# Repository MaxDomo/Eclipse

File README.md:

# Projet Eclipse

Bienvenue sur ce projet de motorisation de la lampe IKEA modèle PS2014

Vous pouvez retrouver l'ensemble de ce projet sur cet [article](https://www.domotioque-passion.fr/).

## Circuits et Schémas

Les circuits et schémas ont été conçus avec KiCad 6.0

## Pièces 3D

Les pièces ont été modélisées à l'aide de SolidWorks 2018.

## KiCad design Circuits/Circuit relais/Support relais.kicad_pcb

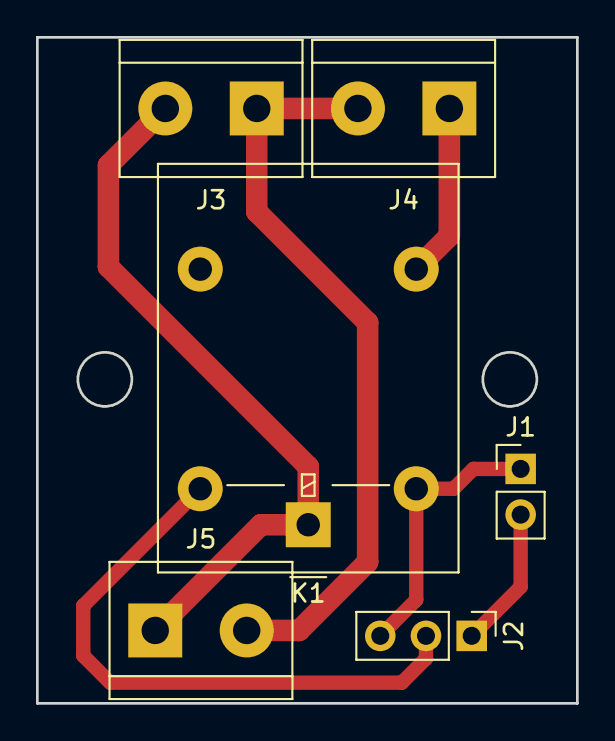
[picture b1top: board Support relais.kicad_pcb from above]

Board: 2 copper layers, 30.0 x 37.0 mm, 6 parts (0 on the bottom side), 6 nets.

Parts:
J1: Conn_Power; PinHeader_1x02_P2.54mm_Vertical
J2: Conn_Power&Control; PinHeader_1x03_P2.54mm_Vertical
J3: AC Input; TerminalBlock_bornier-2_P5.08mm
J4: Light; TerminalBlock_bornier-2_P5.08mm
J5: Transformer; TerminalBlock_bornier-2_P5.08mm
K1: 5V; Relay_SPDT_Omron-G5LE-1

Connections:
unnamed: J1.1, J2.3, K1.2
unnamed: J1.2, J2.1
unnamed: J2.2, K1.5
unnamed: J4.1, K1.3
unnamed: J3.1, J4.2, J5.2
unnamed: J3.2, J5.1, K1.1

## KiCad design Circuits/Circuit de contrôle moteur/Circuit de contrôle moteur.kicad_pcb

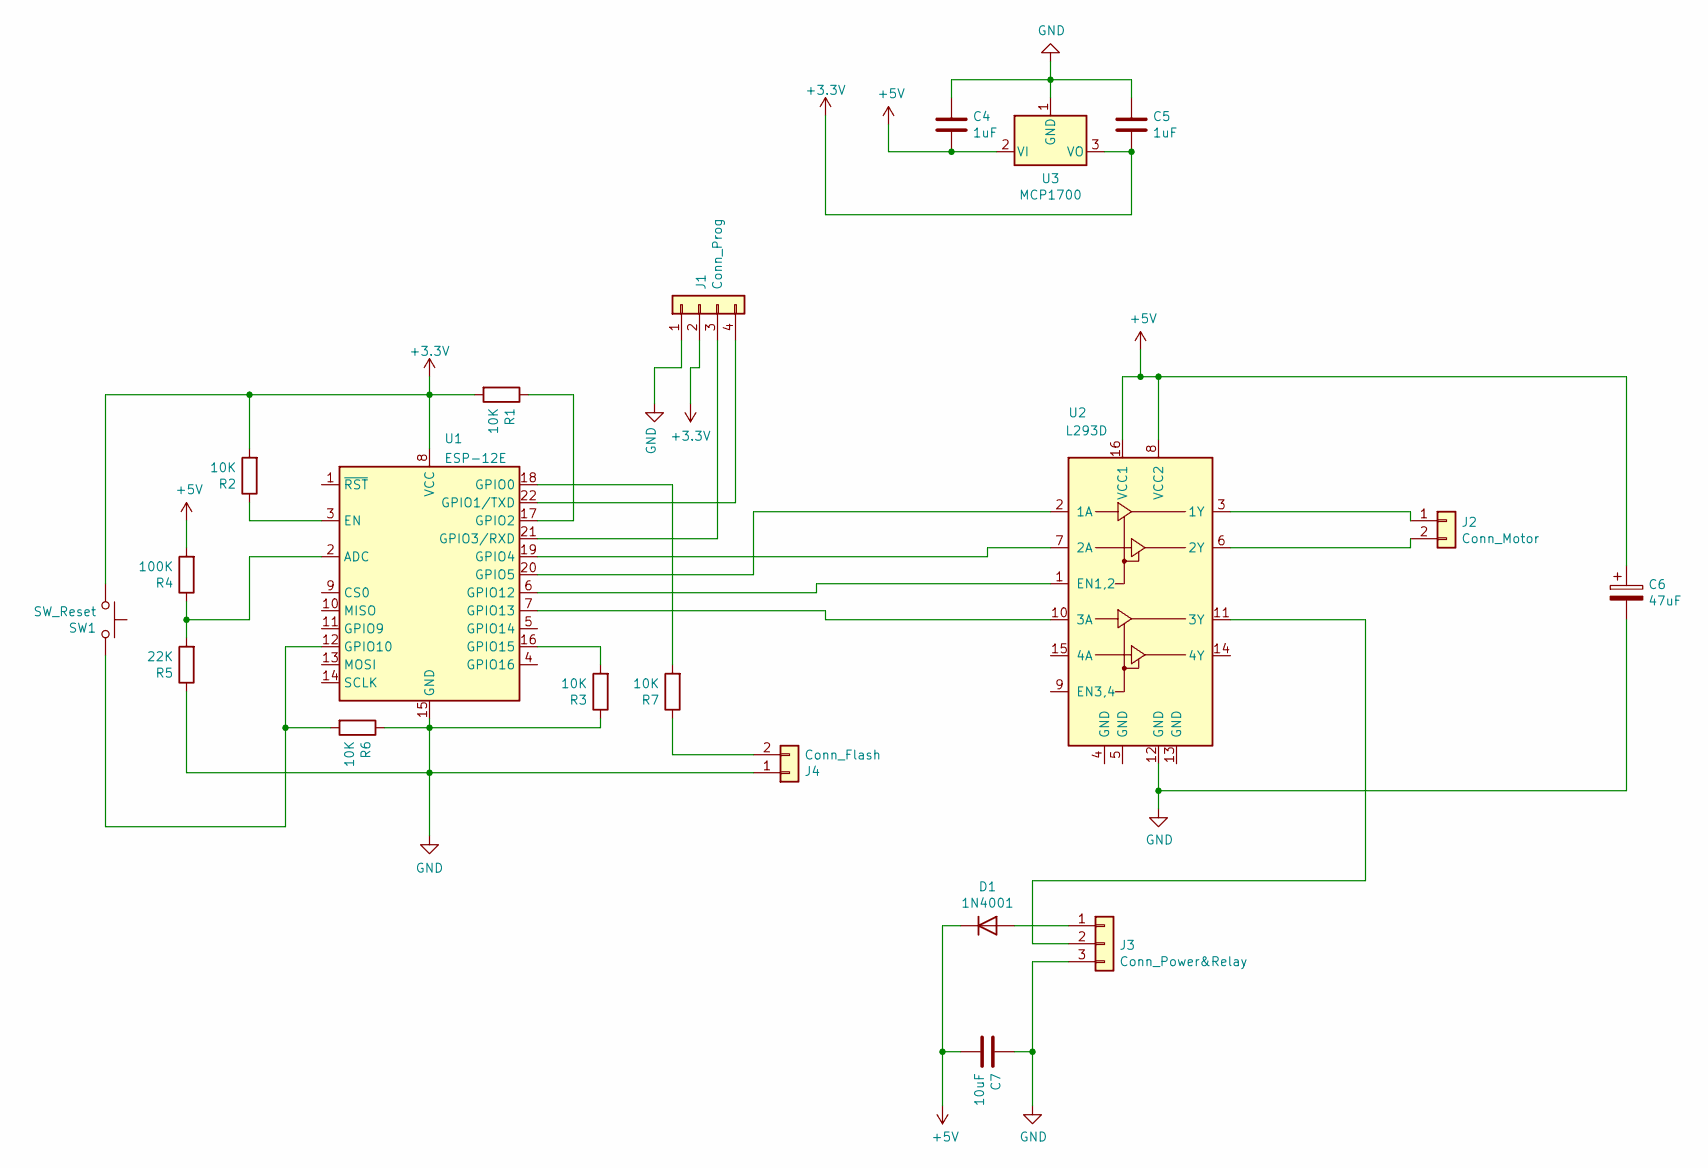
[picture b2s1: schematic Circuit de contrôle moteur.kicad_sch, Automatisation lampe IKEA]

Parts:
C4, C5: 1uF; C_Rect_L4.0mm_W2.5mm_P2.50mm
C6: 47uF; CP_Radial_D5.0mm_P2.50mm
C7: 10uF; C_Rect_L4.0mm_W2.5mm_P2.50mm
D1: 1N4001; D_DO-35_SOD27_P7.62mm_Horizontal
J1: Conn_Prog; PinHeader_1x04_P2.54mm_Vertical
J2: Conn_Motor; PinHeader_1x02_P2.54mm_Vertical
J3: Conn_Power&Relay; PinHeader_1x03_P2.54mm_Vertical
J4: Conn_Flash; PinHeader_1x02_P2.54mm_Vertical
R1, R2, R3, R6, R7: 10K; R_Axial_DIN0204_L3.6mm_D1.6mm_P7.62mm_Horizontal
R4: 100K; R_Axial_DIN0204_L3.6mm_D1.6mm_P7.62mm_Horizontal
R5: 22K; R_Axial_DIN0204_L3.6mm_D1.6mm_P7.62mm_Horizontal
SW1: SW_Reset; SW_PUSH_6mm_H4.3mm
U1: ESP-12E
U2: L293D; DIP-16_W7.62mm
U3: MCP1700; TO-92L_Wide

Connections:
+3V3: C5.2, J1.2, R1.2, R2.2, SW1.1, U1.8 (VCC), U3.3 (VO)
+5V: C4.2, C6.1, C7.2, D1.1 (K), R4.2, U2.8 (VCC2), U2.16 (VCC1), U3.2 (VI)
GND: C4.1, C5.1, C6.2, C7.1, J1.1, J3.3, J4.1, R3.1, R5.1, R6.1, U1.15 (GND), U2.12 (GND), U3.1 (GND)
unnamed: D1.2 (A), J3.1
unnamed: J1.3, U1.21 (GPIO3/RXD)
unnamed: J1.4, U1.22 (GPIO1/TXD)
unnamed: J2.1, U2.3 (1Y)
unnamed: J2.2, U2.6 (2Y)
unnamed: J3.2, U2.11 (3Y)
unnamed: J4.2, R7.1
unnamed: R1.1, U1.17 (GPIO2)
unnamed: R2.1, U1.3 (EN)
unnamed: R3.2, U1.16 (GPIO15)
unnamed: R4.1, R5.2, U1.2 (ADC)
unnamed: R7.2, U1.18 (GPIO0)
unnamed: U1.6 (GPIO12), U2.1 (EN1,2)
unnamed: U1.7 (GPIO13), U2.10 (3A)
unnamed: R6.2, SW1.2, U1.12 (GPIO10)
unnamed: U1.19 (GPIO4), U2.7 (2A)
unnamed: U1.20 (GPIO5), U2.2 (1A)

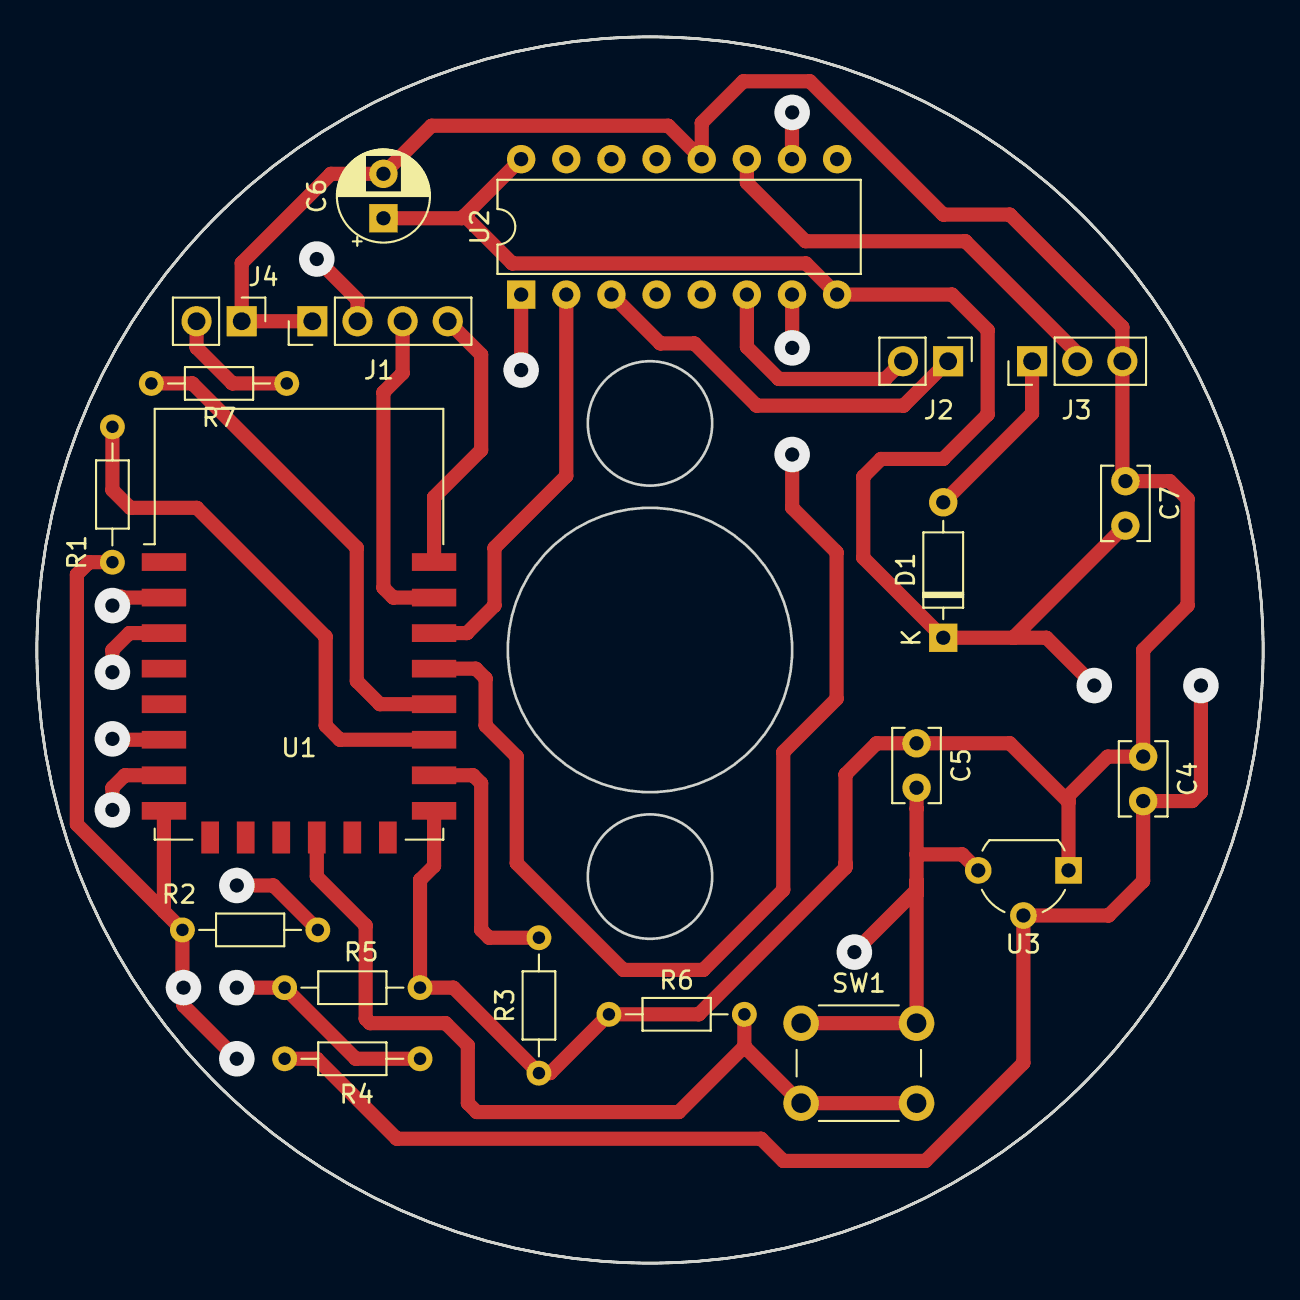
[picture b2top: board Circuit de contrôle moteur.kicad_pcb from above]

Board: 2 copper layers, 69.0 x 69.0 mm, 20 parts (0 on the bottom side), 20 nets.

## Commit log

2022-03-24 first commit :)
2022-05-21 change
    change method
2022-05-21 fix
    fix
